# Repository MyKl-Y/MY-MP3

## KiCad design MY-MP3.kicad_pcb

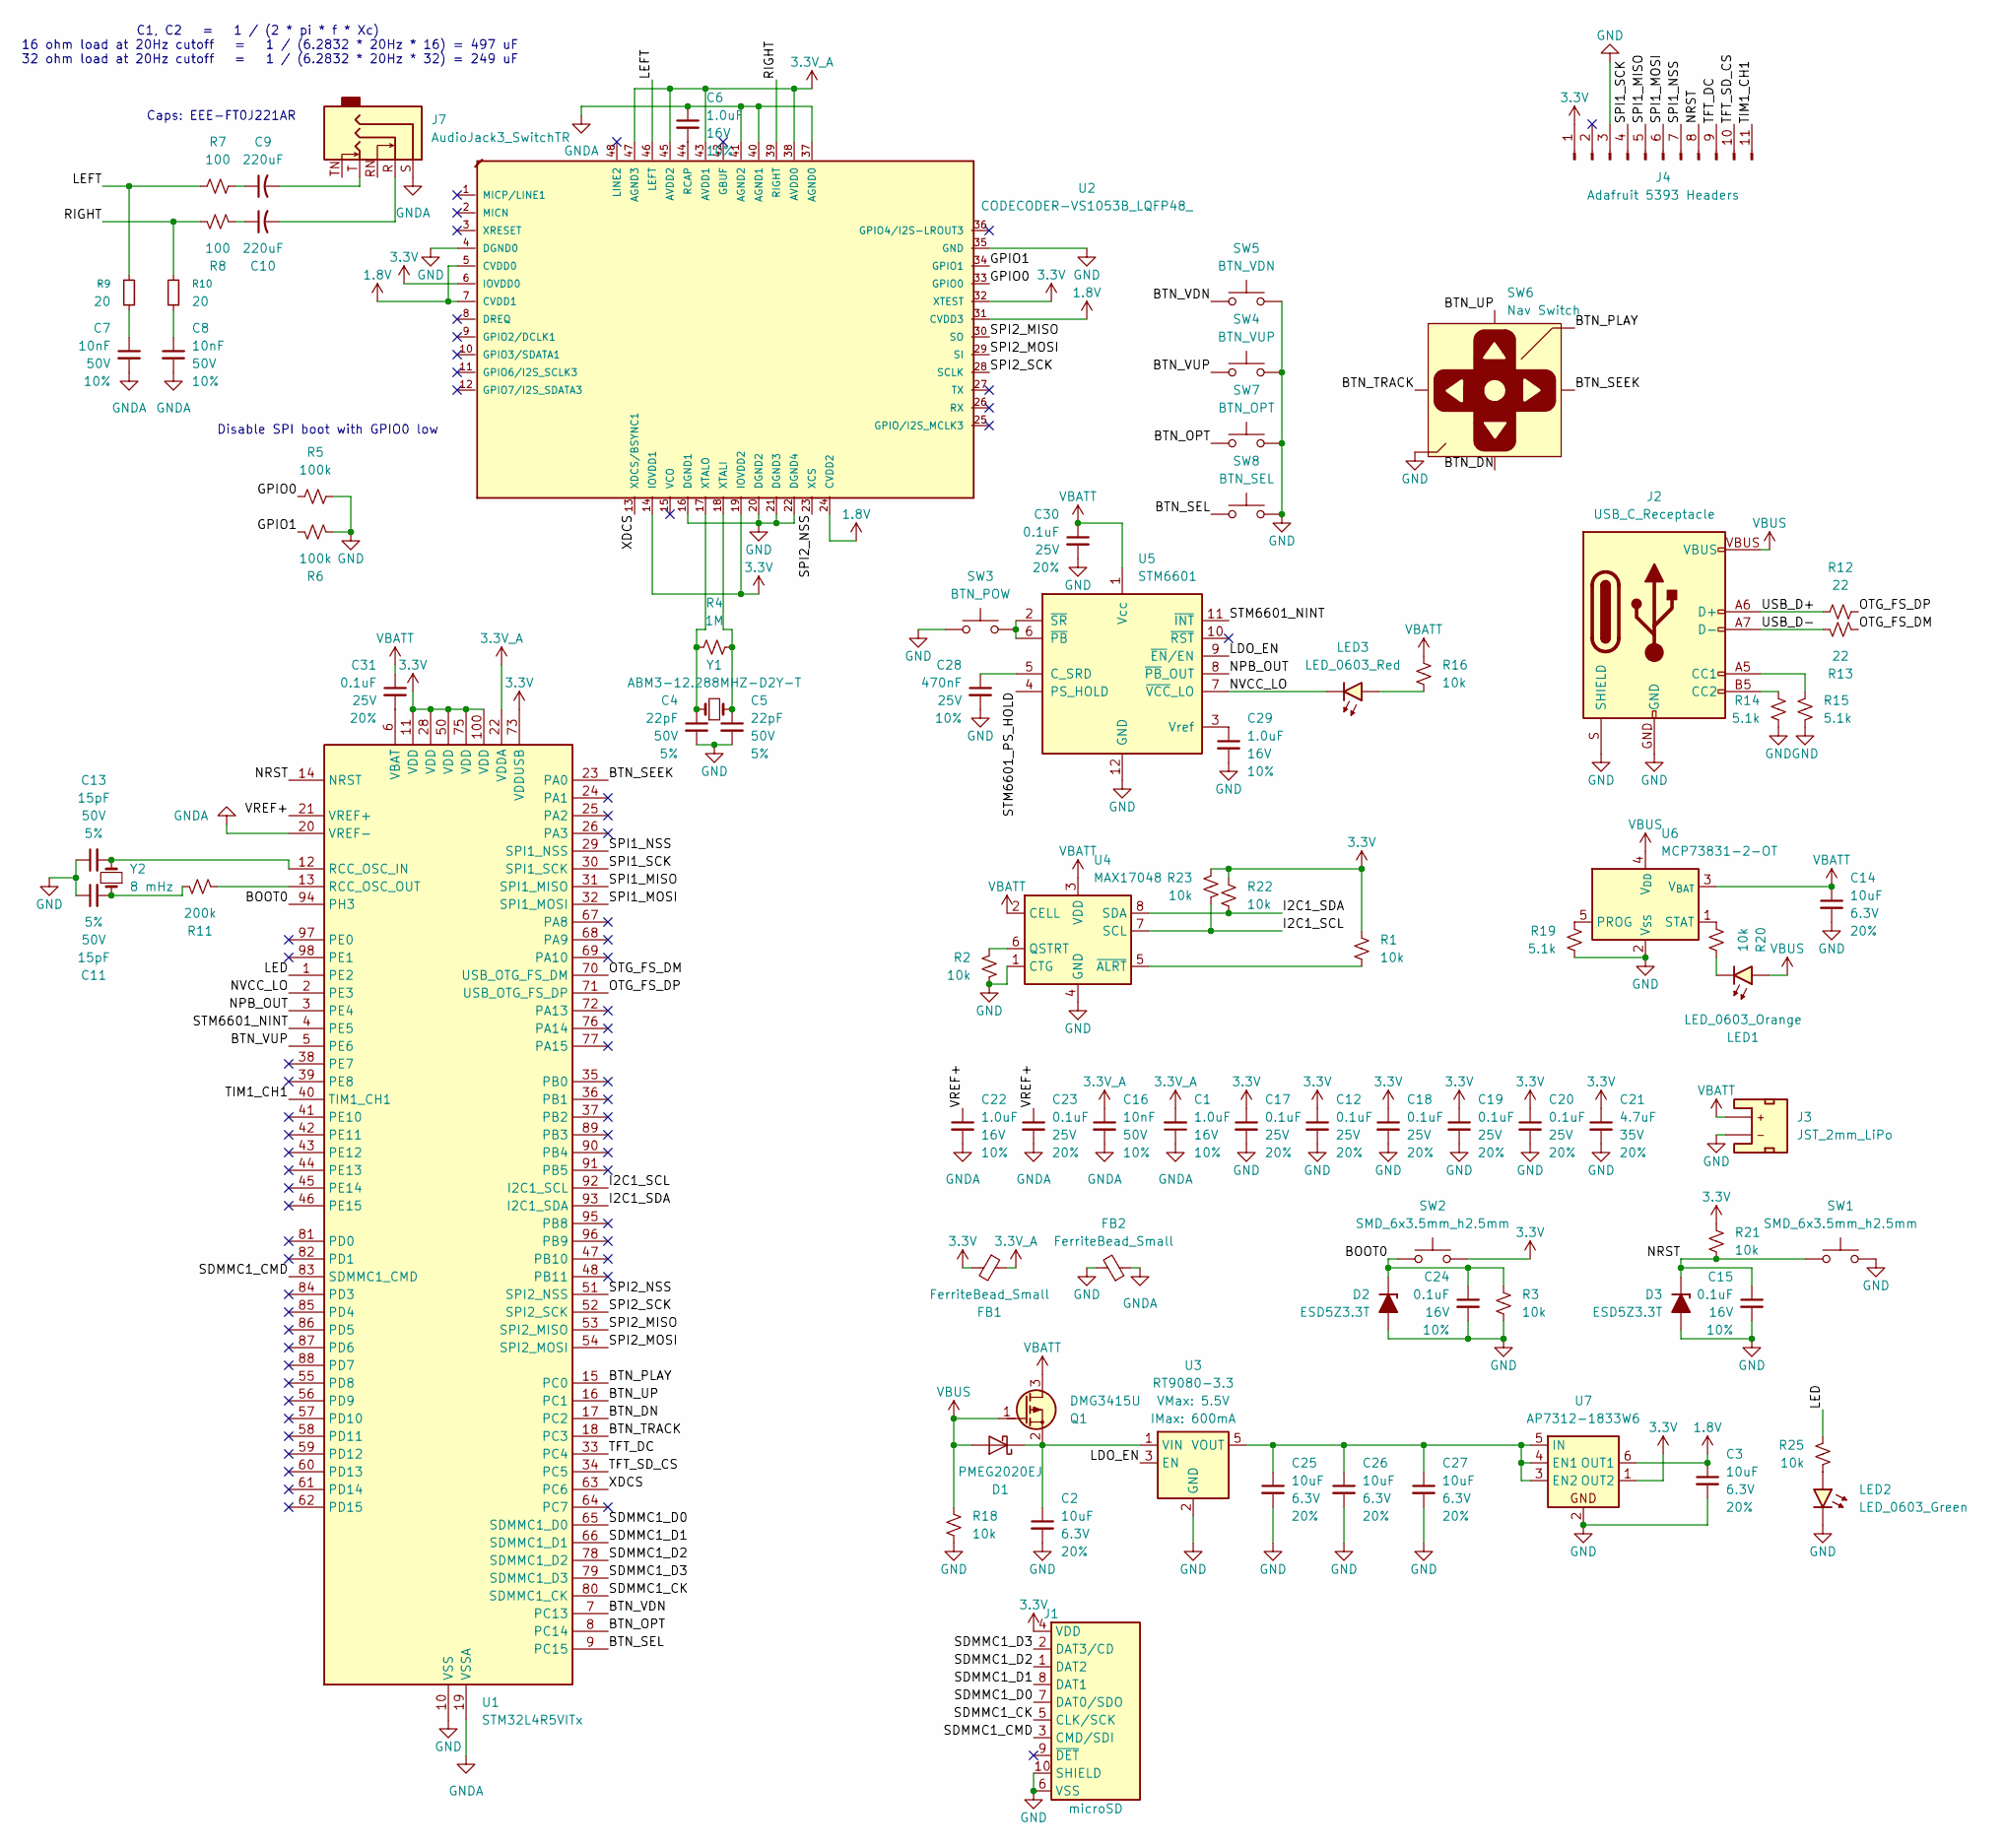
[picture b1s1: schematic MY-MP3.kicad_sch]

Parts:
C1, C6, C22, C29: 1.0uF; C_0402_1005Metric_Pad0.74x0.62mm; Voltage 16V; Tolerance 10%
C2, C3, C14, C25, C26, C27: 10uF; C_0402_1005Metric_Pad0.74x0.62mm; Voltage 6.3V; Tolerance 20%
C4, C5: 22pF; C_0402_1005Metric_Pad0.74x0.62mm; Voltage 50V; Tolerance 5%
C7, C8, C16: 10nF; C_0402_1005Metric_Pad0.74x0.62mm; Voltage 50V; Tolerance 10%
C9, C10: 220uF; CP_Elec_5x5.8
C11, C13: 15pF; C_0402_1005Metric_Pad0.74x0.62mm; Voltage 50V; Tolerance 5%
C12, C17, C18, C19, C20, C23, C30, C31: 0.1uF; C_0402_1005Metric_Pad0.74x0.62mm; Voltage 25V; Tolerance 20%
C15, C24: 0.1uF; C_0402_1005Metric_Pad0.74x0.62mm; Voltage 16V; Tolerance 10%
C21: 4.7uF; C_0402_1005Metric_Pad0.74x0.62mm; Voltage 35V; Tolerance 20%
C28: 470nF; C_0402_1005Metric_Pad0.74x0.62mm; Voltage 25V; Tolerance 10%
D1: PMEG2020EJ; D_SOD-323F
D2, D3: ESD5Z3.3T; D_SOD-523
FB1, FB2: FerriteBead_Small; L_0402_1005Metric_Pad0.77x0.64mm_HandSolder
J1: microSD; microSD_External_Pin
J2: USB_C_Receptacle; USB-C_16
J3: JST_2mm_LiPo; JST_1x02_P2.0mm_Horizontal_SMD
J4: Adafruit 5393 Headers; PinSocket_1x11_P2.54mm_Vertical
J7: AudioJack3_SwitchTR; Jack_3.5mm_CUI_SJ1-3525N_Horizontal
LED1: LED_0603_Orange; LED_0402_1005Metric_Orange
LED2: LED_0603_Green; LED_0402_1005Metric_Green
LED3: LED_0603_Red; LED_0402_1005Metric_Red
Q1: DMG3415U; SOT-23
R1, R2, R3, R16, R18, R20, R21, R22, R23, R25: 10k; R_0402_1005Metric
R4: 1M; R_0402_1005Metric
R5, R6: 100k; R_0402_1005Metric
R7, R8: 100; R_0402_1005Metric
R9, R10: 20; R_0201_0603Metric_Pad0.64x0.40mm_HandSolder
R11: 200k; R_0402_1005Metric
R12, R13: 22; R_0402_1005Metric
R14, R15, R19: 5.1k; R_0402_1005Metric
SW1, SW2: SMD_6x3.5mm_h2.5mm; Push_SMD_6x3.5mm; Mfg Part# 8-004 SMD Button 8x3.6mm Height=2.5mm
SW3: BTN_POW; Push_SMD_RA_4.5x3.4mm
SW4: BTN_VUP; Push_SMD_RA_4.5x3.4mm
SW5: BTN_VDN; Push_SMD_RA_4.5x3.4mm
SW6: Nav Switch; Navigation_SMD_9.9x9.9mm
SW7: BTN_OPT; Push_SMD_6x3.5mm; Mfg Part# 8-004 SMD Button 8x3.6mm Height=2.5mm
SW8: BTN_SEL; Push_SMD_6x3.5mm; Mfg Part# 8-004 SMD Button 8x3.6mm Height=2.5mm
U1: STM32L4R5VITx; LQFP-100_14x14mm_P0.5mm
U2: CODECODER-VS1053B_LQFP48_; LQFP-48_7x7mm_P0.5mm; MPN VS1053B
U3: RT9080-3.3; SOT23-5
U4: MAX17048; DFN-8_2x2mm_P0.5mm_EP1.2x0.8mm
U5: STM6601; TDFN-12_2x3mm_P0.5mm
U6: MCP73831-2-OT; SOT-23-5
U7: AP7312-1833W6; SOT-23-6
Y1: ABM3-12.288MHZ-D2Y-T; Crystal_SMD_Abracon_ABM3-2Pin_5.0x3.2mm_HandSoldering
Y2: 8 mHz; Crystal_SMD_Abracon_ABM3-2Pin_5.0x3.2mm_HandSoldering

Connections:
1.8V: C3.1, U2.5 (CVDD0), U2.7 (CVDD1), U2.24 (CVDD2), U2.31 (CVDD3), U7.6 (OUT1)
3.3V: C12.1, C17.1, C18.1, C19.1, C20.1, C21.1, FB1.2, J1.4 (VDD), J4.1, R1.2, R21.1, R22.2, R23.2, SW2.1, U1.11 (VDD), U1.28 (VDD), U1.50 (VDD), U1.73 (VDDUSB), U1.75 (VDD), U1.100 (VDD), U2.6 (IOVDD0), U2.14 (IOVDD1), U2.19 (IOVDD2), U2.32 (XTEST), U7.1 (OUT2)
3.3V_A: C1.2, C16.1, FB1.1, U1.22 (VDDA), U2.38 (AVDD0), U2.43 (AVDD1), U2.45 (AVDD2), U2.47 (AGND3)
/BOOT0: C24.1, D2.1 (K), R3.1, SW2.2, U1.94 (PH3)
/BTN_DN: SW6.5 (Down), U1.17 (PC2)
/BTN_OPT: SW7.1, U1.8 (PC14)
/BTN_PLAY: SW6.4 (Center), U1.15 (PC0)
/BTN_SEEK: SW6.2 (Right), U1.23 (PA0)
/BTN_SEL: SW8.1, U1.9 (PC15)
/BTN_TRACK: SW6.7 (Left), U1.18 (PC3)
/BTN_UP: SW6.1 (Up), U1.16 (PC1)
/BTN_VDN: SW5.1, U1.7 (PC13)
/BTN_VUP: SW4.1, U1.5 (PE6)
/GPIO0: R5.1, U2.33 (GPIO0)
/GPIO1: R6.1, U2.34 (GPIO1)
/I2C1_SCL: R23.1, U1.92 (I2C1_SCL), U4.7 (SCL)
/I2C1_SDA: R22.1, U1.93 (I2C1_SDA), U4.8 (SDA)
/LDO_EN: U3.3 (EN), U5.9 (~EN/EN)
/LED: R25.2, U1.1 (PE2)
/LEFT: R7.1, R9.1, U2.46 (LEFT)
/NPB_OUT: U1.3 (PE4), U5.8 (~PB_OUT)
/NRST: C15.1, D3.1 (K), J4.8, R21.2, SW1.1, U1.14 (NRST)
/NVCC_LO: LED3.1 (K), U1.2 (PE3), U5.7 (~VCC_LO)
/OTG_FS_DM: R13.2, U1.70 (USB_OTG_FS_DM)
/OTG_FS_DP: R12.2, U1.71 (USB_OTG_FS_DP)
/RIGHT: R8.1, R10.1, U2.39 (RIGHT)
/SDMMC1_CK: J1.5 (CLK/SCK), U1.80 (SDMMC1_CK)
/SDMMC1_CMD: J1.3 (CMD/SDI), U1.83 (SDMMC1_CMD)
/SDMMC1_D0: J1.7 (DAT0/SDO), U1.65 (SDMMC1_D0)
/SDMMC1_D1: J1.8 (DAT1), U1.66 (SDMMC1_D1)
/SDMMC1_D2: J1.1 (DAT2), U1.78 (SDMMC1_D2)
/SDMMC1_D3: J1.2 (DAT3/CD), U1.79 (SDMMC1_D3)
/SPI1_MISO: J4.5, U1.31 (SPI1_MISO)
/SPI1_MOSI: J4.6, U1.32 (SPI1_MOSI)
/SPI1_NSS: J4.7, U1.29 (SPI1_NSS)
/SPI1_SCK: J4.4, U1.30 (SPI1_SCK)
/SPI2_MISO: U1.53 (SPI2_MISO), U2.30 (SO)
/SPI2_MOSI: U1.54 (SPI2_MOSI), U2.29 (SI)
/SPI2_NSS: U1.51 (SPI2_NSS), U2.23 (XCS)
/SPI2_SCK: U1.52 (SPI2_SCK), U2.28 (SCLK)
/STM6601_NINT: U1.4 (PE5), U5.11 (~INT)
/STM6601_PS_HOLD: U5.4 (PS_HOLD)
/TFT_DC: J4.9, U1.33 (PC4)
/TFT_SD_CS: J4.10, U1.34 (PC5)
/TIM1_CH1: J4.11, U1.40 (TIM1_CH1)
/USB_D+: J2.A6 (D+), J2.B6 (D+), R12.1
/USB_D-: J2.A7 (D-), J2.B7 (D-), R13.1
/VREF+: C22.1, C23.1, U1.21 (VREF+)
/XDCS: U1.63 (PC6), U2.13 (XDCS/BSYNC1)
GND: C2.2, C3.2, C4.2, C5.2, C11.1, C12.2, C13.1, C14.2, C15.2, C17.2, C18.2, C19.2, C20.2, C21.2, C24.2, C25.2, C26.2, C27.2, C28.2, C29.2, C30.2, D2.2 (A), D3.2 (A), FB2.2, J1.6 (VSS), J1.10 (SHIELD), J2.GND, J2.S (SHIELD), J3.1 (-), J4.3, LED2.1 (K), R2.1, R3.2, R5.2, R6.2, R14.1, R15.1, R18.1, R19.1, SW1.2, SW3.1, SW4.2, SW5.2, SW6.3 (GND), SW6.6 (GND), SW6.8 (GND), SW6.9 (GND), SW6.10 (GND), SW7.2, SW8.2, U1.10 (VSS), U1.27 (VSS), U1.49 (VSS), U1.74 (VSS), U1.99 (VSS), U2.4 (DGND0), U2.16 (DGND1), U2.20 (DGND2), U2.21 (DGND3), U2.22 (DGND4), U2.35 (GND), U3.2 (GND), U4.1 (CTG), U4.4 (GND), U4.9 (GND), U5.12 (GND), U6.2 (V_{SS}), U7.2
GNDA: C1.1, C6.1, C7.2, C8.2, C16.2, C22.2, C23.2, FB2.1, J7.S, U1.19 (VSSA), U1.20 (VREF-), U2.37 (AGND0), U2.40 (AGND1), U2.41 (AGND2)
unnamed: C7.1, R9.2
unnamed: C8.1, R10.2
unnamed: C9.1, R7.2
unnamed: C9.2, J7.T
unnamed: C10.1, R8.2
unnamed: C10.2, J7.R
unnamed: C11.2, R11.2, Y2.1
unnamed: C2.1, D1.1 (K), Q1.2 (S), U3.1 (VIN)
unnamed: J2.A5 (CC1), R15.2
unnamed: J2.B5 (CC2), R14.2
unnamed: LED1.1 (K), R20.1
unnamed: LED2.2 (A), R25.1
unnamed: LED3.2 (A), R16.1
unnamed: C13.2, U1.12 (RCC_OSC_IN), Y2.2
unnamed: R11.1, U1.13 (RCC_OSC_OUT)
unnamed: C31.2, U1.6 (VBAT)
unnamed: C6.2, U2.44 (RCAP)
unnamed: C5.1, R4.2, U2.18 (XTALI), Y1.2
unnamed: C4.1, R4.1, U2.17 (XTALO), Y1.1
unnamed: C25.1, C26.1, C27.1, U3.5 (VOUT), U7.3 (EN2), U7.4 (EN1), U7.5 (IN)
unnamed: R2.2, U4.6 (QSTRT)
unnamed: R1.1, U4.5 (~ALRT)
unnamed: C28.1, U5.5 (C_SRD)
unnamed: C29.1, U5.3 (Vref)
unnamed: SW3.2, U5.2 (~SR), U5.6 (~PB)
unnamed: R19.2, U6.5 (PROG)
unnamed: R20.2, U6.1 (STAT)
VBATT: C14.1, C30.1, C31.1, J3.2 (+), Q1.3 (D), R16.2, U4.2 (CELL), U4.3 (VDD), U5.1 (Vcc), U6.3 (V_{BAT})
VBUS: D1.2 (A), J2.VBUS, LED1.2 (A), Q1.1 (G), R18.2, U6.4 (V_{DD})

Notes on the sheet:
Disable SPI boot with GPIO0 low
C1, C2 = 1 / (2 * pi * f * Xc) 16 ohm load at 20Hz cutoff = 1 / (6.2832 * 20Hz * 16) = 497 uF 32 ohm load at 20Hz cutoff = 1 / (6.2832 * 20Hz * 32) = 249 uF
Caps: EEE-FT0J221AR

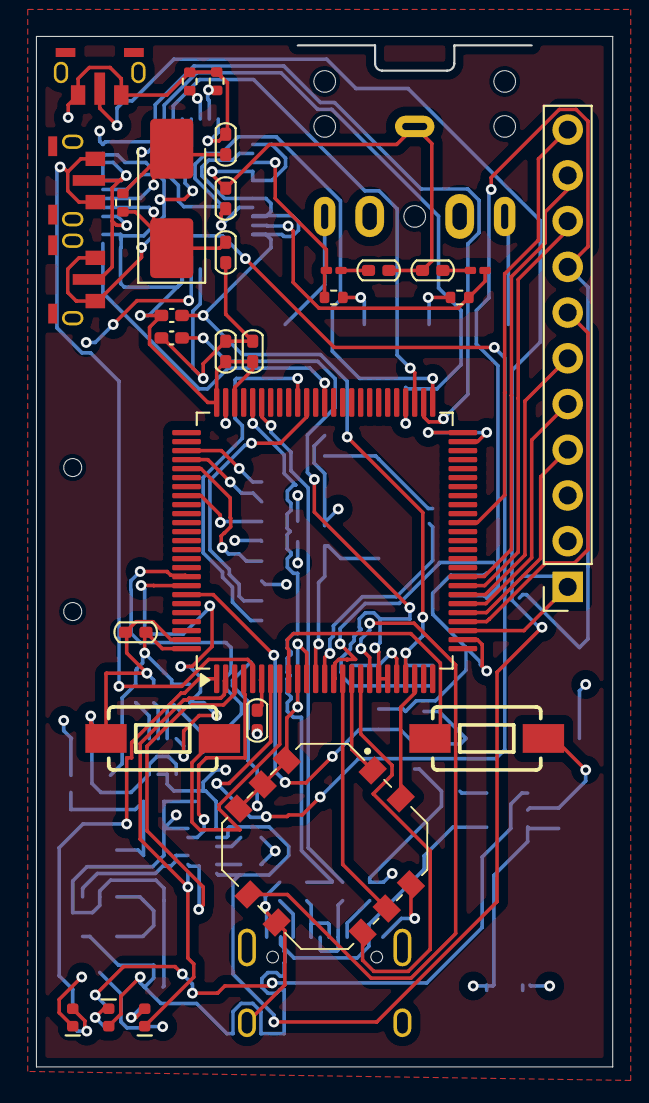
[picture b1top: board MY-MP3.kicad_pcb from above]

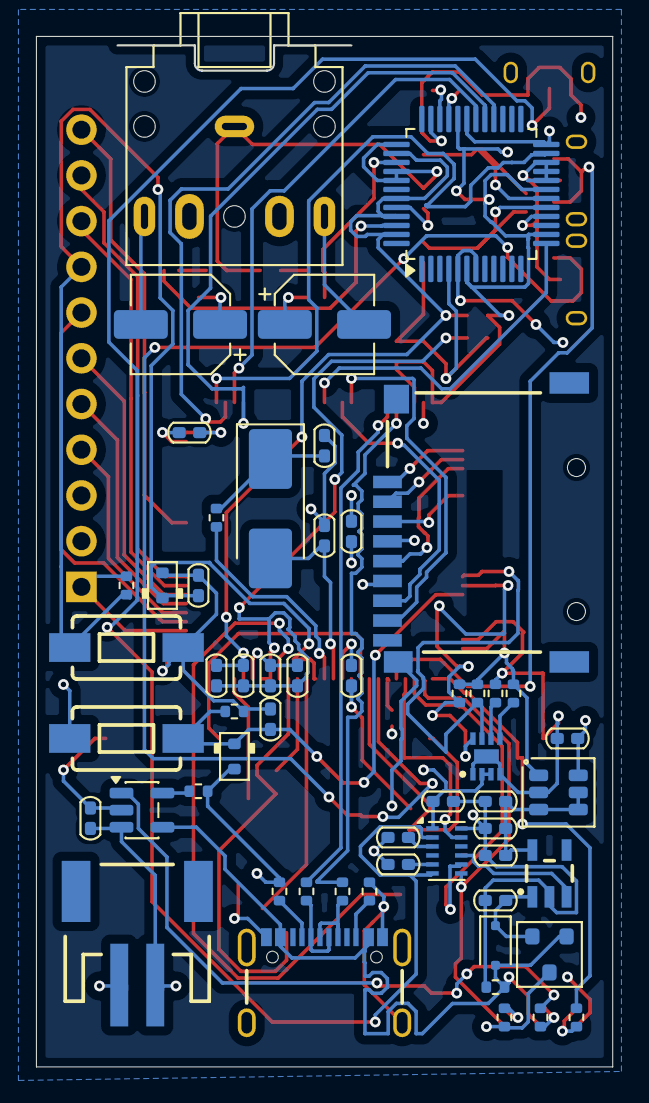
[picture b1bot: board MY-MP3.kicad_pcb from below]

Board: 4 copper layers, 31.9 x 57.2 mm, 85 parts (55 on the bottom side), 79 nets.

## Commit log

2025-10-24 'Finished' schematic for MP3 player
2025-10-28 Added some buttons and started the on off hardware functionallity
2025-10-28 Finish Schematic and start PCB
2025-10-29 Finish PCB
2025-10-29 Redo PCB for smaller size and better bin placements
